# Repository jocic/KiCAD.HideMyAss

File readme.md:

# HideMyAss

**Song of the project:** [Judas Priest - Breaking The Law](https://www.youtube.com/watch?v=L397TWLwrUU)

*  LoJack (173 MHz)
*  SM (925 – 960 MHz)
*  DCS (1805 – 1880 MHz)
*  3G (2100 – 2170 MHz )
*  4G Low (790 – 870 MHz)
*  4G High (2600 – 2690 MHz)
*  5G F1 (450 MHz to 6 GHz)
*  5G F2 (24.25 GHz to 52.6 GHz)
*  WiFi (2400 – 2500 MHz)
*  GPS L1 (1570 – 1580 MHz)
*  GPS L2 (1220 – 1230 MHz)
*  Bluetooth (2.402 GHz - 2.480 GHz)

When finished, device can be ordered directly from my website.

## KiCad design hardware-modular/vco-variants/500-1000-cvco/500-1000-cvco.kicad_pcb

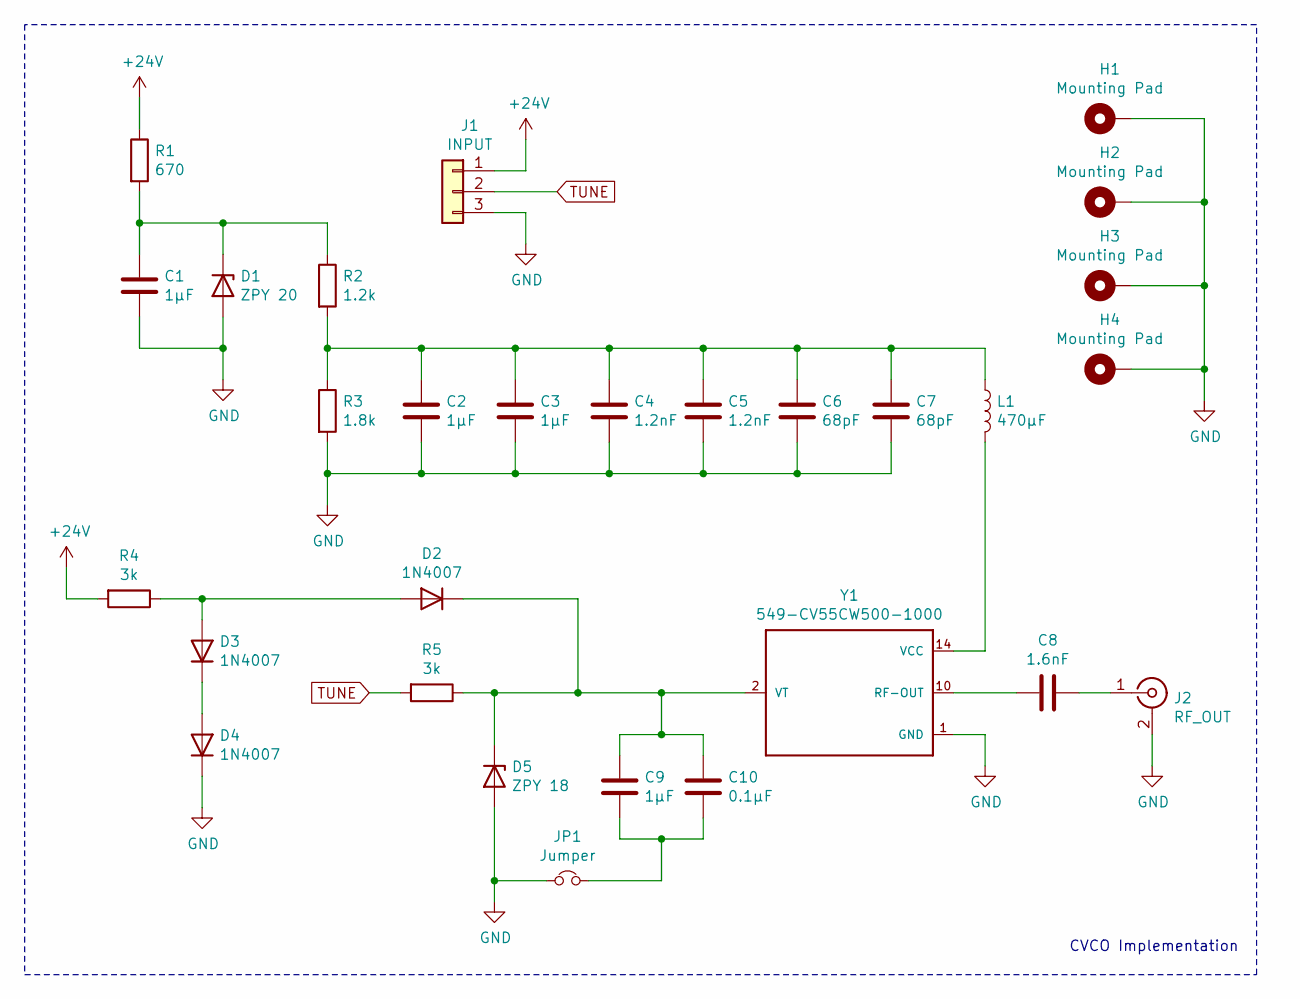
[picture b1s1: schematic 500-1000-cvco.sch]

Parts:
C1: 1μF; C_Disc_D3.0mm_W1.6mm_P2.50mm
C2, C3, C9: 1μF; C_0805_2012Metric
C4, C5: 1.2nF; C_0805_2012Metric
C6, C7: 68pF; C_0805_2012Metric
C8: 1.6nF; C_0805_2012Metric
C10: 0.1μF; C_0805_2012Metric
D1: ZPY 20; D_DO-41_SOD81_P2.54mm_Vertical_AnodeUp
D2, D3, D4: 1N4007; D_DO-41_SOD81_P2.54mm_Vertical_AnodeUp
D5: ZPY 18; D_DO-41_SOD81_P2.54mm_Vertical_AnodeUp
H1, H2, H3, H4: Mounting Pad; MountingHole_3.2mm_M3_Pad_Via
J1: INPUT; TerminalBlock_4Ucon_1x03_P3.50mm_Vertical
J2: RF_OUT; SMA_Amphenol_132289_EdgeMount
JP1: Jumper; PinHeader_1x02_P2.54mm_Vertical
L1: 470μF; L_0805_2012Metric
R1: 670; R_Axial_DIN0309_L9.0mm_D3.2mm_P15.24mm_Horizontal
R2: 1.2k; R_Axial_DIN0207_L6.3mm_D2.5mm_P10.16mm_Horizontal
R3: 1.8k; R_Axial_DIN0207_L6.3mm_D2.5mm_P10.16mm_Horizontal
R4, R5: 3k; R_Axial_DIN0207_L6.3mm_D2.5mm_P10.16mm_Horizontal
Y1: 549-CV55CW500-1000; CVCO55

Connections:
+24V: J1.1, R1.1, R4.2
GND: C1.2, C2.2, C3.2, C4.2, C5.2, C6.2, C7.2, D1.2 (A), D4.1 (K), D5.2 (A), H1.1, H2.1, H3.1, H4.1, J1.3, J2.2 (Ext), JP1.1, R3.2, Y1.1 (GND), Y1.3 (GND), Y1.4 (GND), Y1.5 (GND), Y1.6 (GND), Y1.7 (GND), Y1.8 (GND), Y1.9 (GND), Y1.11 (GND), Y1.12 (GND), Y1.13 (GND), Y1.15 (GND), Y1.16 (GND)
unnamed: C1.1, D1.1 (K), R1.2, R2.1
unnamed: C2.1, C3.1, C4.1, C5.1, C6.1, C7.1, L1.1, R2.2, R3.1
unnamed: C8.1, J2.1 (In)
unnamed: C8.2, Y1.10 (RF-OUT)
unnamed: C9.1, C10.1, D2.1 (K), D5.1 (K), R5.1, Y1.2 (VT)
unnamed: C9.2, C10.2, JP1.2
unnamed: D2.2 (A), D3.2 (A), R4.1
unnamed: D3.1 (K), D4.2 (A)
unnamed: L1.2, Y1.14 (VCC)
TUNE: J1.2, R5.2

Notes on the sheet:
CVCO Implementation

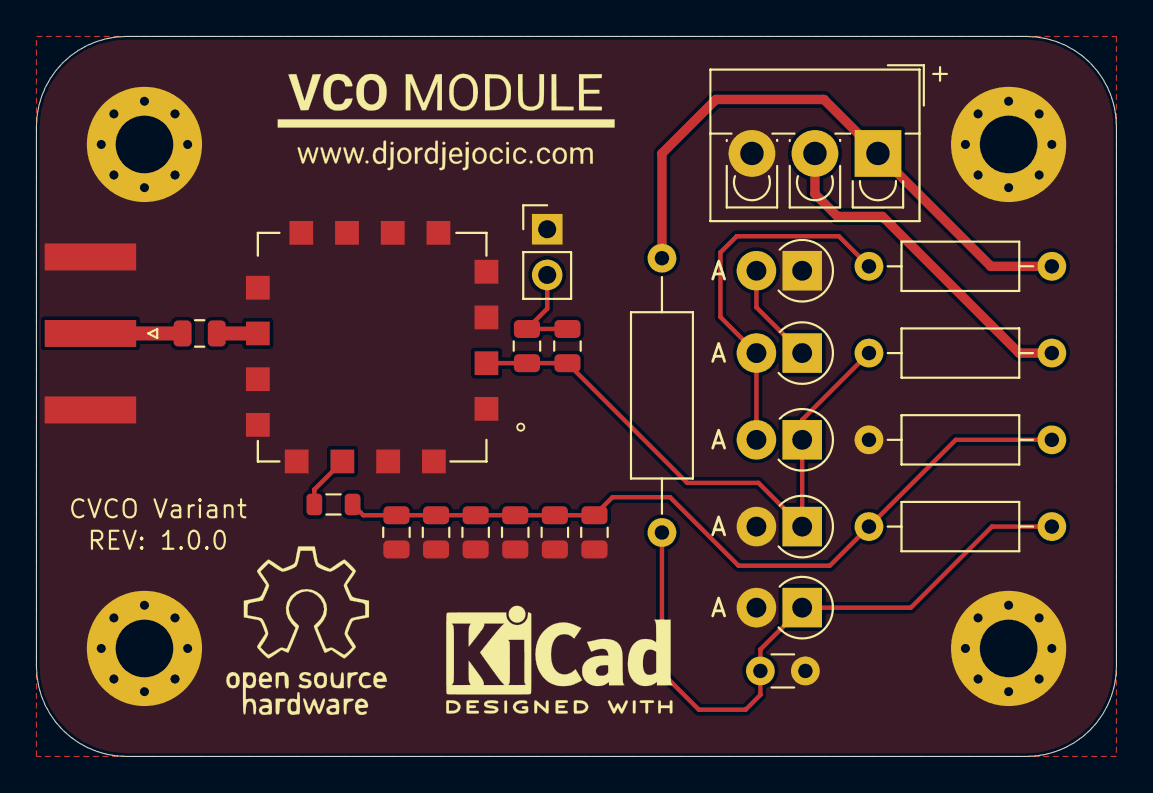
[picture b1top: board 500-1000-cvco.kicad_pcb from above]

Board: 2 copper layers, 60.0 x 40.0 mm, 29 parts (0 on the bottom side), 12 nets.

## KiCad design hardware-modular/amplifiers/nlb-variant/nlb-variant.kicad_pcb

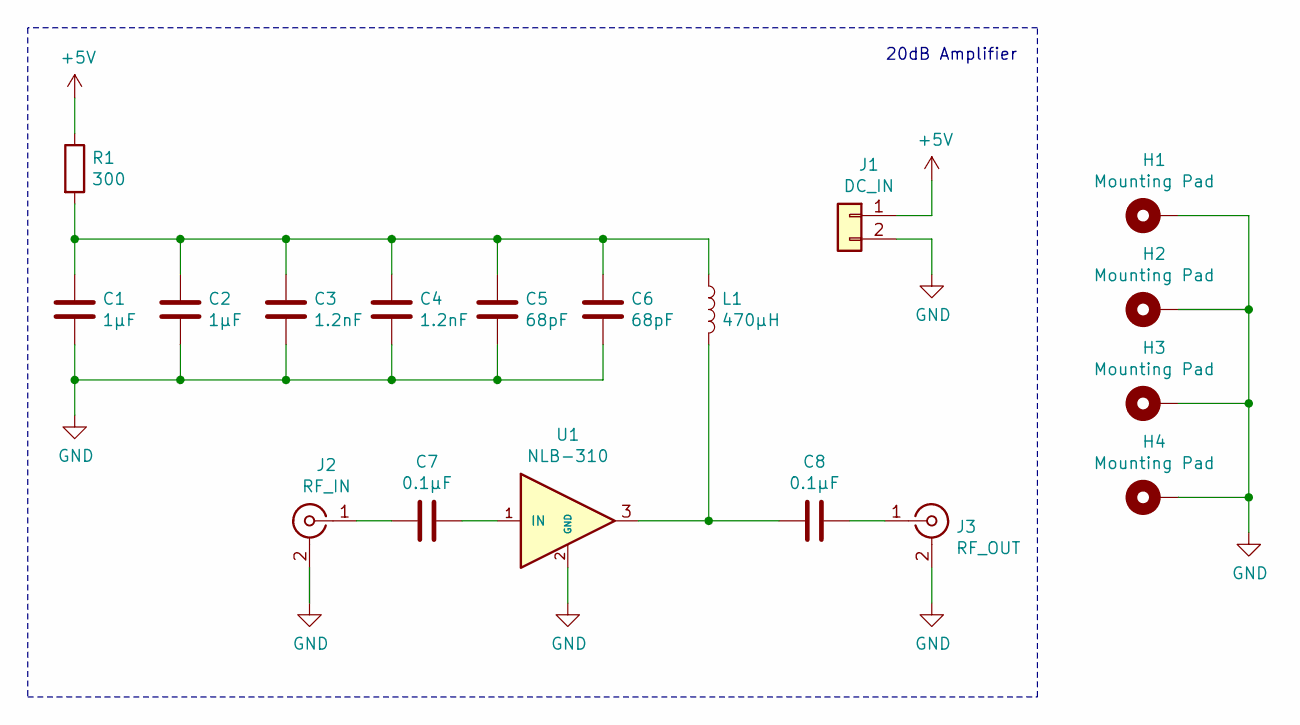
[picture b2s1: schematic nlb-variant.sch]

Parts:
C1, C2: 1μF; C_0805_2012Metric
C3, C4: 1.2nF; C_0805_2012Metric
C5, C6: 68pF; C_0805_2012Metric
C7, C8: 0.1μF; C_0805_2012Metric
H1, H2, H3, H4: Mounting Pad; MountingHole_3.2mm_M3_Pad_Via
J1: DC_IN; TerminalBlock_4Ucon_1x02_P3.50mm_Horizontal
J2: RF_IN; SMA_Amphenol_132289_EdgeMount
J3: RF_OUT; SMA_Amphenol_132289_EdgeMount
L1: 470μH; L_0805_2012Metric
R1: 300; R_0805_2012Metric
U1: NLB-310; Micro-X-4

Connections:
+5V: J1.1, R1.1
GND: C1.2, C2.2, C3.2, C4.2, C5.2, C6.2, H1.1, H2.1, H3.1, H4.1, J1.2, J2.2 (Ext), J3.2 (Ext), U1.2 (GND), U1.4 (GND)
unnamed: C1.1, C2.1, C3.1, C4.1, C5.1, C6.1, L1.1, R1.2
unnamed: C7.1, J2.1 (In)
unnamed: C7.2, U1.1 (IN)
unnamed: C8.1, L1.2, U1.3
unnamed: C8.2, J3.1 (In)

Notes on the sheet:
20dB Amplifier

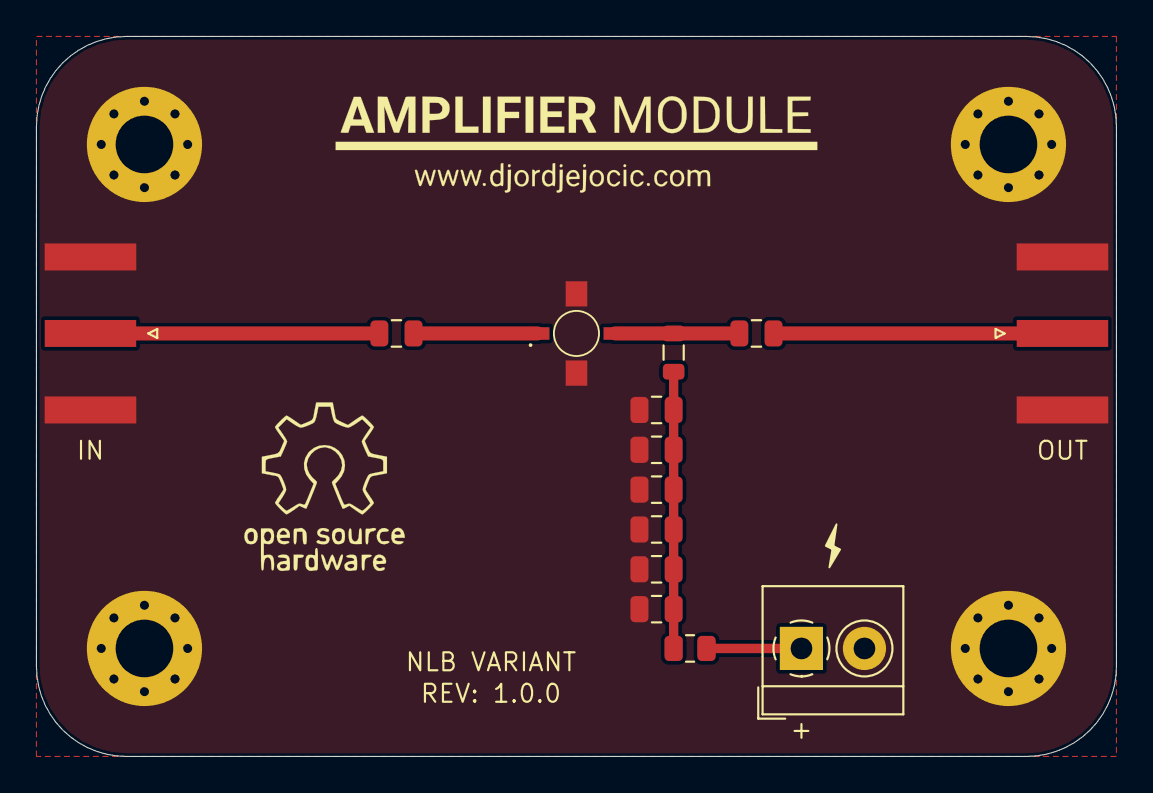
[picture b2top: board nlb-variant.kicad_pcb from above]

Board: 2 copper layers, 60.0 x 40.0 mm, 18 parts (0 on the bottom side), 7 nets.

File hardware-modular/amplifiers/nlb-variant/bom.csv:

Reference, Quantity, Value, Footprint, Datasheet
C1 C2 ,2,"1μF","Capacitor_SMD:C_0805_2012Metric","~"
C3 C4 ,2,"1.2nF","Capacitor_SMD:C_0805_2012Metric","~"
C5 C6 ,2,"68pF","Capacitor_SMD:C_0805_2012Metric","~"
C7 C8 ,2,"0.1μF","Capacitor_SMD:C_0805_2012Metric","~"
H1 H2 H3 H4 ,4,"Mounting Pad","MountingHole:MountingHole_3.2mm_M3_Pad_Via","~"
J1 ,1,"DC_IN","TerminalBlock_4Ucon:TerminalBlock_4Ucon_1x02_P3.50mm_Horizontal","~"
J2 ,1,"RF_IN","Connector_Coaxial:SMA_Amphenol_132289_EdgeMount"," ~"
J3 ,1,"RF_OUT","Connector_Coaxial:SMA_Amphenol_132289_EdgeMount"," ~"
L1 ,1,"470μH","Inductor_SMD:L_0805_2012Metric","~"
R1 ,1,"300","Resistor_SMD:R_0805_2012Metric","~"
U1 ,1,"NLB-310","CVCO:Micro-X-4",""

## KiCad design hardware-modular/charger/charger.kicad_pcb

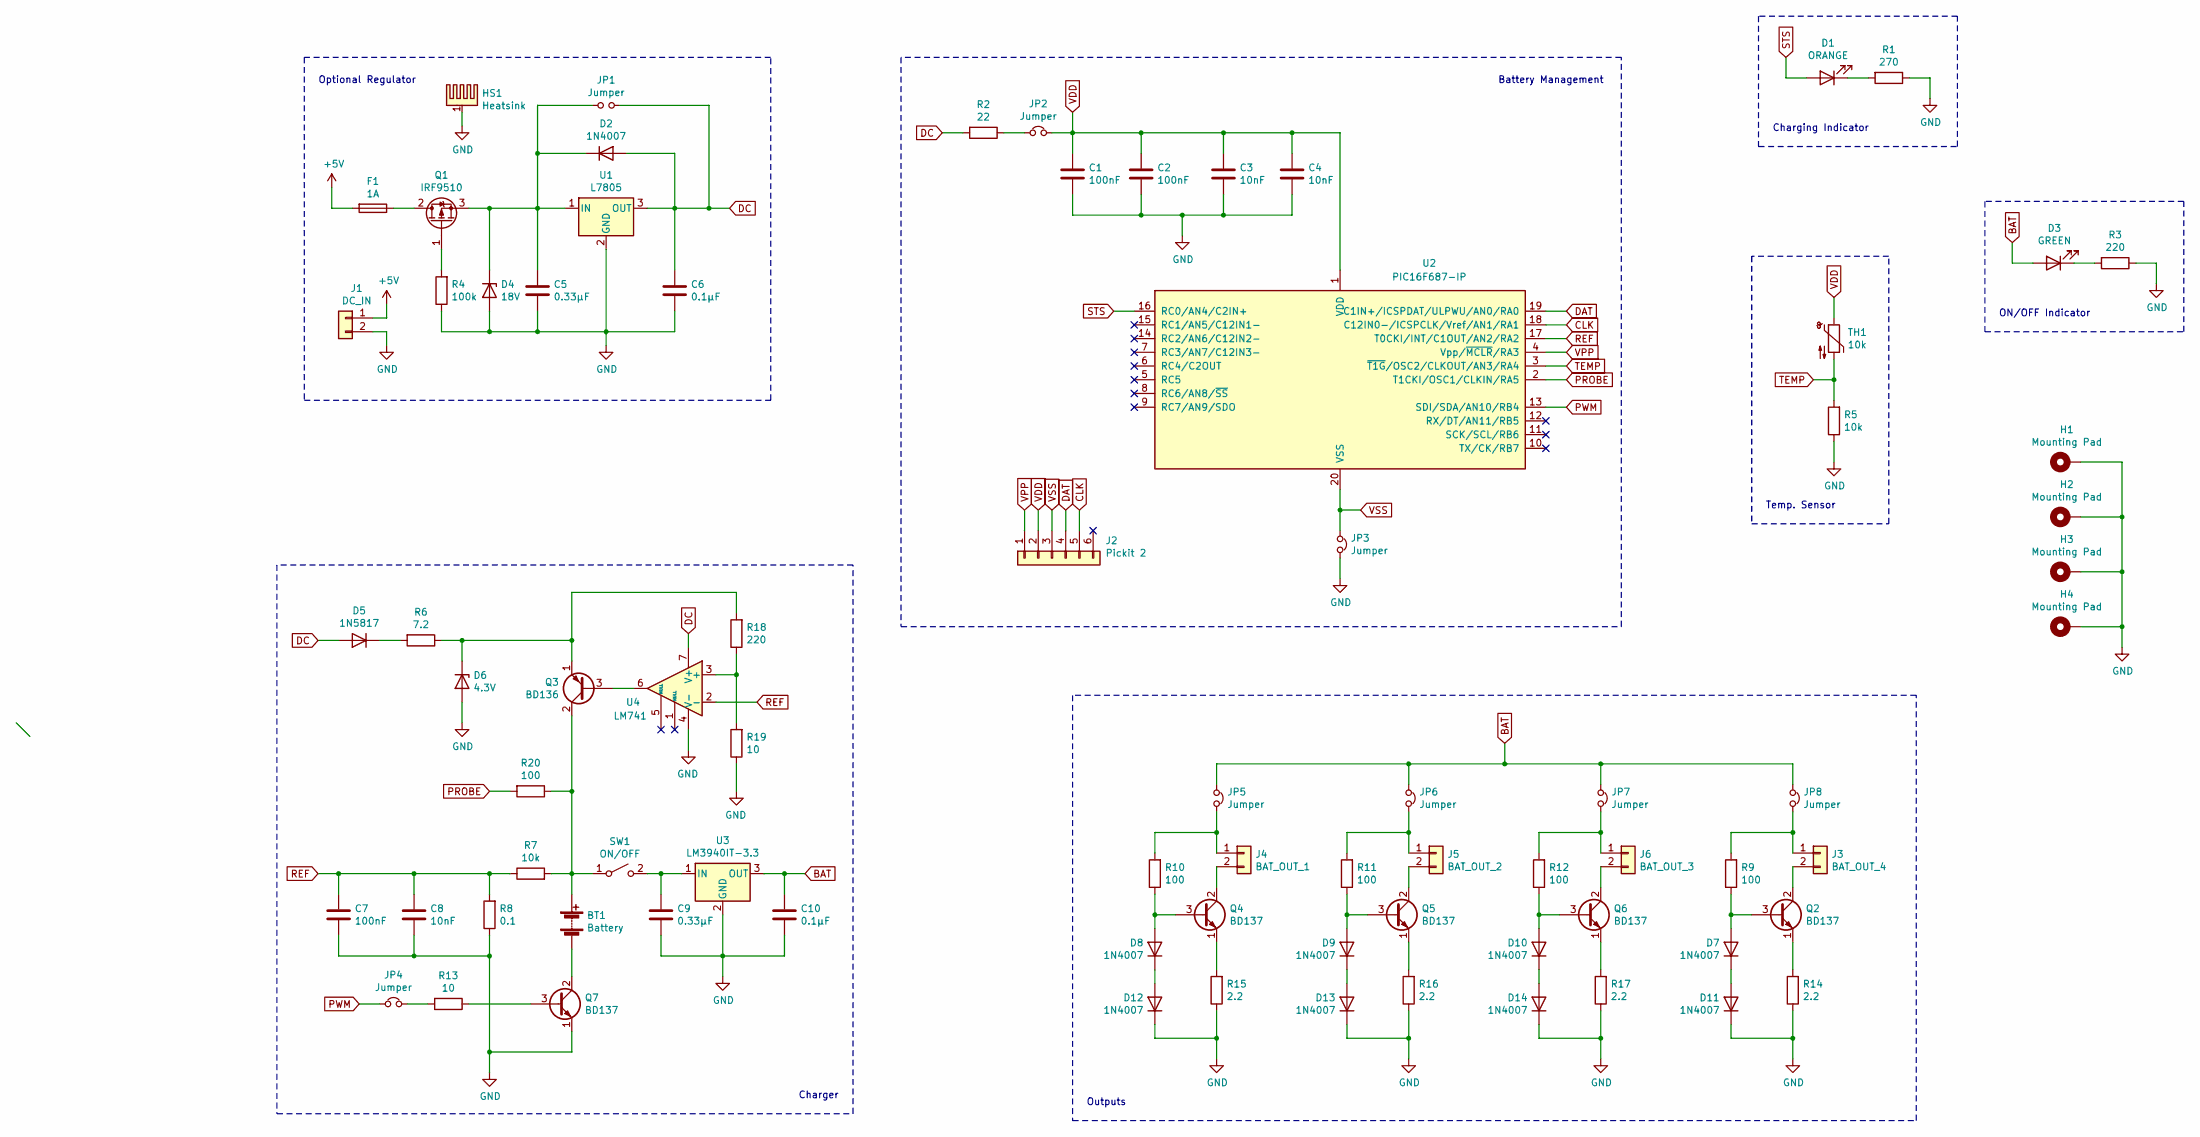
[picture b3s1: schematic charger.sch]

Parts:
BT1: Battery; TerminalBlock_4Ucon_1x02_P3.50mm_Horizontal
C1, C2, C7: 100nF; C_Disc_D3.0mm_W1.6mm_P2.50mm
C3, C4, C8: 10nF; C_Disc_D3.0mm_W1.6mm_P2.50mm
C5, C9: 0.33μF; C_Disc_D3.0mm_W1.6mm_P2.50mm
C6, C10: 0.1μF; C_Disc_D3.0mm_W1.6mm_P2.50mm
D1: ORANGE; Molex_KK-254_AE-6410-02A_1x02_P2.54mm_Vertical
D2, D7, D8, D9, D10, D11, D12, D13, D14: 1N4007; D_DO-41_SOD81_P10.16mm_Horizontal
D3: GREEN; Molex_KK-254_AE-6410-02A_1x02_P2.54mm_Vertical
D4: 18V; D_DO-41_SOD81_P10.16mm_Horizontal
D5: 1N5817; D_DO-41_SOD81_P10.16mm_Horizontal
D6: 4.3V; D_DO-41_SOD81_P10.16mm_Horizontal
F1: 1A; Fuseholder_Cylinder-5x20mm_Stelvio-Kontek_PTF78_Horizontal_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
H1, H2, H3, H4: Mounting Pad; MountingHole_3.2mm_M3_Pad_Via
HS1: Heatsink; Heatsink_Fischer_SK104-STCB_35x13mm__2xDrill3.5mm_ScrewM3
J1: DC_IN; TerminalBlock_4Ucon_1x02_P3.50mm_Horizontal
J2: Pickit 2; PinSocket_1x06_P2.54mm_Vertical
J3: BAT_OUT_4; TerminalBlock_4Ucon_1x02_P3.50mm_Horizontal
J4: BAT_OUT_1; TerminalBlock_4Ucon_1x02_P3.50mm_Horizontal
J5: BAT_OUT_2; TerminalBlock_4Ucon_1x02_P3.50mm_Horizontal
J6: BAT_OUT_3; TerminalBlock_4Ucon_1x02_P3.50mm_Horizontal
JP1, JP2, JP3, JP4, JP5, JP6, JP7, JP8: Jumper; PinHeader_1x02_P2.54mm_Vertical
Q1: IRF9510; TO-220-3_Vertical
Q2, Q4, Q5, Q6, Q7: BD137; TO-126-3_Vertical
Q3: BD136; TO-126-3_Vertical
R1: 270; R_Axial_DIN0207_L6.3mm_D2.5mm_P10.16mm_Horizontal
R2: 22; R_Axial_DIN0414_L11.9mm_D4.5mm_P5.08mm_Vertical
R3, R18: 220; R_Axial_DIN0207_L6.3mm_D2.5mm_P10.16mm_Horizontal
R4: 100k; R_Axial_DIN0207_L6.3mm_D2.5mm_P10.16mm_Horizontal
R5, R7: 10k; R_Axial_DIN0207_L6.3mm_D2.5mm_P10.16mm_Horizontal
R6: 7.2; R_Axial_DIN0516_L15.5mm_D5.0mm_P5.08mm_Vertical
R8: 0.1; R_Axial_DIN0207_L6.3mm_D2.5mm_P10.16mm_Horizontal
R9, R10, R11, R12, R20: 100; R_Axial_DIN0207_L6.3mm_D2.5mm_P10.16mm_Horizontal
R13, R19: 10; R_Axial_DIN0207_L6.3mm_D2.5mm_P10.16mm_Horizontal
R14, R15, R16, R17: 2.2; R_Axial_DIN0207_L6.3mm_D2.5mm_P10.16mm_Horizontal
SW1: ON/OFF; Molex_KK-254_AE-6410-02A_1x02_P2.54mm_Vertical
TH1: 10k; Molex_KK-254_AE-6410-02A_1x02_P2.54mm_Vertical
U1: L7805; TO-220-3_Vertical
U2: PIC16F687-IP; DIP-20_W7.62mm_Socket
U3: LM3940IT-3.3; TO-220-3_Vertical
U4: LM741; DIP-8_W7.62mm_Socket

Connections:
+5V: F1.2, J1.1
BAT: C10.1, D3.2 (A), JP5.1, JP6.1, JP7.1, JP8.1, U3.3 (OUT)
CLK: J2.5, U2.18 (C12IN0-/ICSPCLK/Vref/AN1/RA1)
DAT: J2.4, U2.19 (C1IN+/ICSPDAT/ULPWU/AN0/RA0)
DC: C6.1, D2.2 (A), D5.2 (A), JP1.2, R2.2, U1.3 (OUT), U4.7 (V+)
GND: C1.2, C2.2, C3.2, C4.2, C5.2, C6.2, C7.2, C8.2, C9.2, C10.2, D4.2 (A), D6.2 (A), D11.1 (K), D12.1 (K), D13.1 (K), D14.1 (K), H1.1, H2.1, H3.1, H4.1, HS1.1, J1.2, JP3.2, Q7.1 (E), R1.1, R3.1, R4.1, R5.1, R8.1, R14.1, R15.1, R16.1, R17.1, R19.1, U1.2 (GND), U3.2 (GND), U4.4 (V-)
unnamed: BT1.1 (+), Q3.2 (C), R7.2, R20.1, SW1.1 (A)
unnamed: BT1.2 (-), Q7.2 (C)
unnamed: C5.1, D2.1 (K), D4.1 (K), JP1.1, Q1.3 (S), U1.1 (IN)
unnamed: C9.1, SW1.2 (B), U3.1 (IN)
unnamed: D1.1 (K), R1.2
unnamed: D3.1 (K), R3.2
unnamed: D5.1 (K), R6.2
unnamed: D6.1 (K), Q3.1 (E), R6.1, R18.2
unnamed: D7.2 (A), Q2.3 (B), R9.1
unnamed: D8.2 (A), Q4.3 (B), R10.1
unnamed: D9.2 (A), Q5.3 (B), R11.1
unnamed: D10.1 (K), D14.2 (A)
unnamed: D10.2 (A), Q6.3 (B), R12.1
unnamed: D7.1 (K), D11.2 (A)
unnamed: D8.1 (K), D12.2 (A)
unnamed: D9.1 (K), D13.2 (A)
unnamed: F1.1, Q1.2 (D)
unnamed: J3.1, JP8.2, R9.2
unnamed: J3.2, Q2.2 (C)
unnamed: J4.1, JP5.2, R10.2
unnamed: J4.2, Q4.2 (C)
unnamed: J5.1, JP6.2, R11.2
unnamed: J5.2, Q5.2 (C)
unnamed: J6.1, JP7.2, R12.2
unnamed: J6.2, Q6.2 (C)
unnamed: JP2.1, R2.1
unnamed: JP4.2, R13.2
unnamed: Q1.1 (G), R4.2
unnamed: Q2.1 (E), R14.2
unnamed: Q3.3 (B), U4.6
unnamed: Q4.1 (E), R15.2
unnamed: Q5.1 (E), R16.2
unnamed: Q6.1 (E), R17.2
unnamed: Q7.3 (B), R13.1
unnamed: R18.1, R19.2, U4.3 (+)
PROBE: R20.2, U2.2 (T1CKI/OSC1/CLKIN/RA5)
PWM: JP4.1, U2.13 (SDI/SDA/AN10/RB4)
REF: C7.1, C8.1, R7.1, R8.2, U2.17 (T0CKI/INT/C1OUT/AN2/RA2), U4.2 (-)
STS: D1.2 (A), U2.16 (RC0/AN4/C2IN+)
TEMP: R5.2, TH1.2, U2.3 (~T1G~/OSC2/CLKOUT/AN3/RA4)
VDD: C1.1, C2.1, C3.1, C4.1, J2.2, JP2.2, TH1.1, U2.1 (VDD)
VPP: J2.1, U2.4 (Vpp/~MCLR~/RA3)
VSS: J2.3, JP3.1, U2.20 (VSS)

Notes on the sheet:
Charging Indicator
Temp. Sensor
Optional Regulator
Battery Management
ON/OFF Indicator
Outputs
Charger

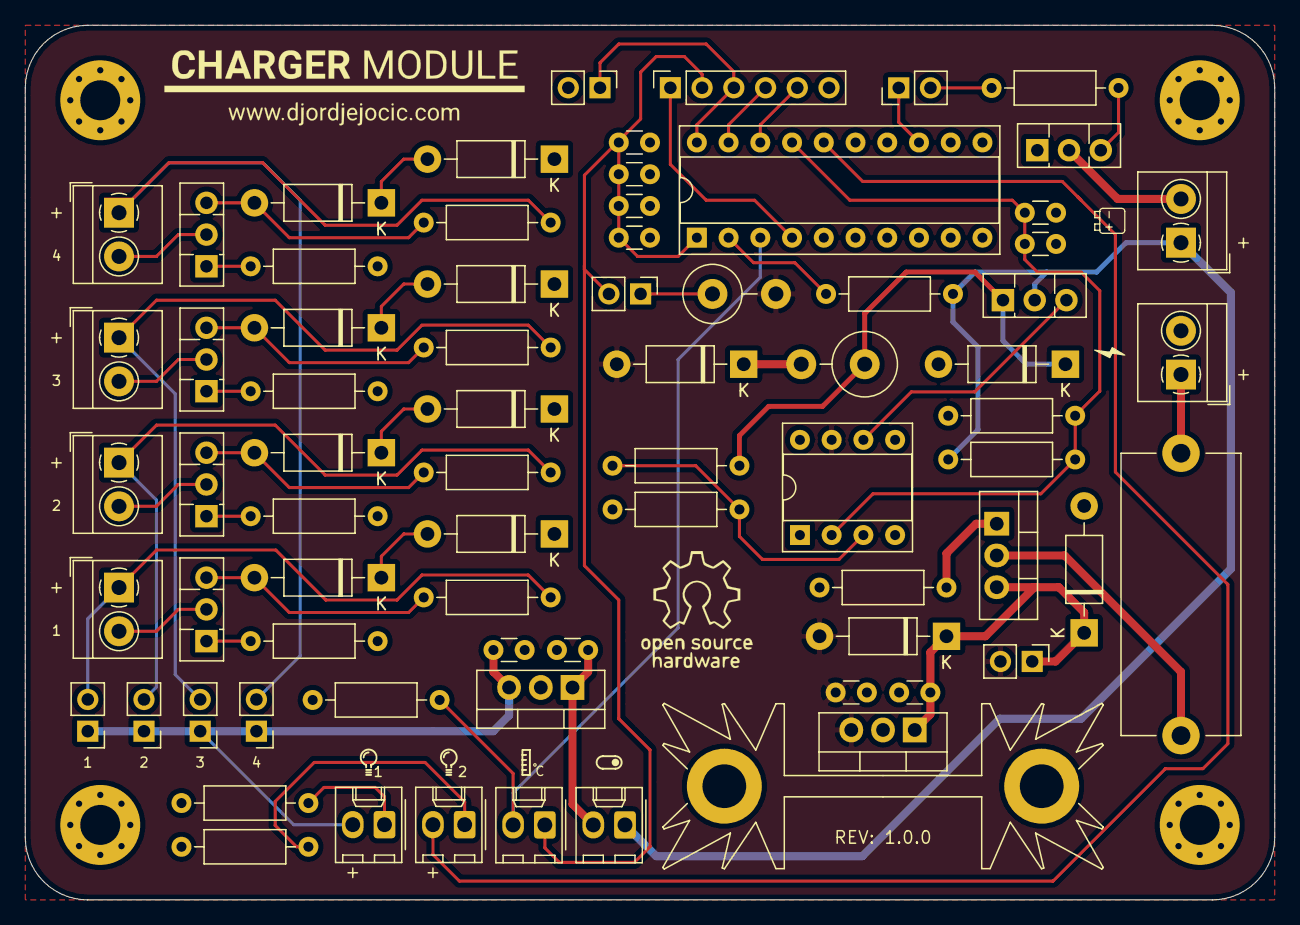
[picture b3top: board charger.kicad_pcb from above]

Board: 2 copper layers, 100.0 x 70.0 mm, 78 parts (0 on the bottom side), 49 nets.

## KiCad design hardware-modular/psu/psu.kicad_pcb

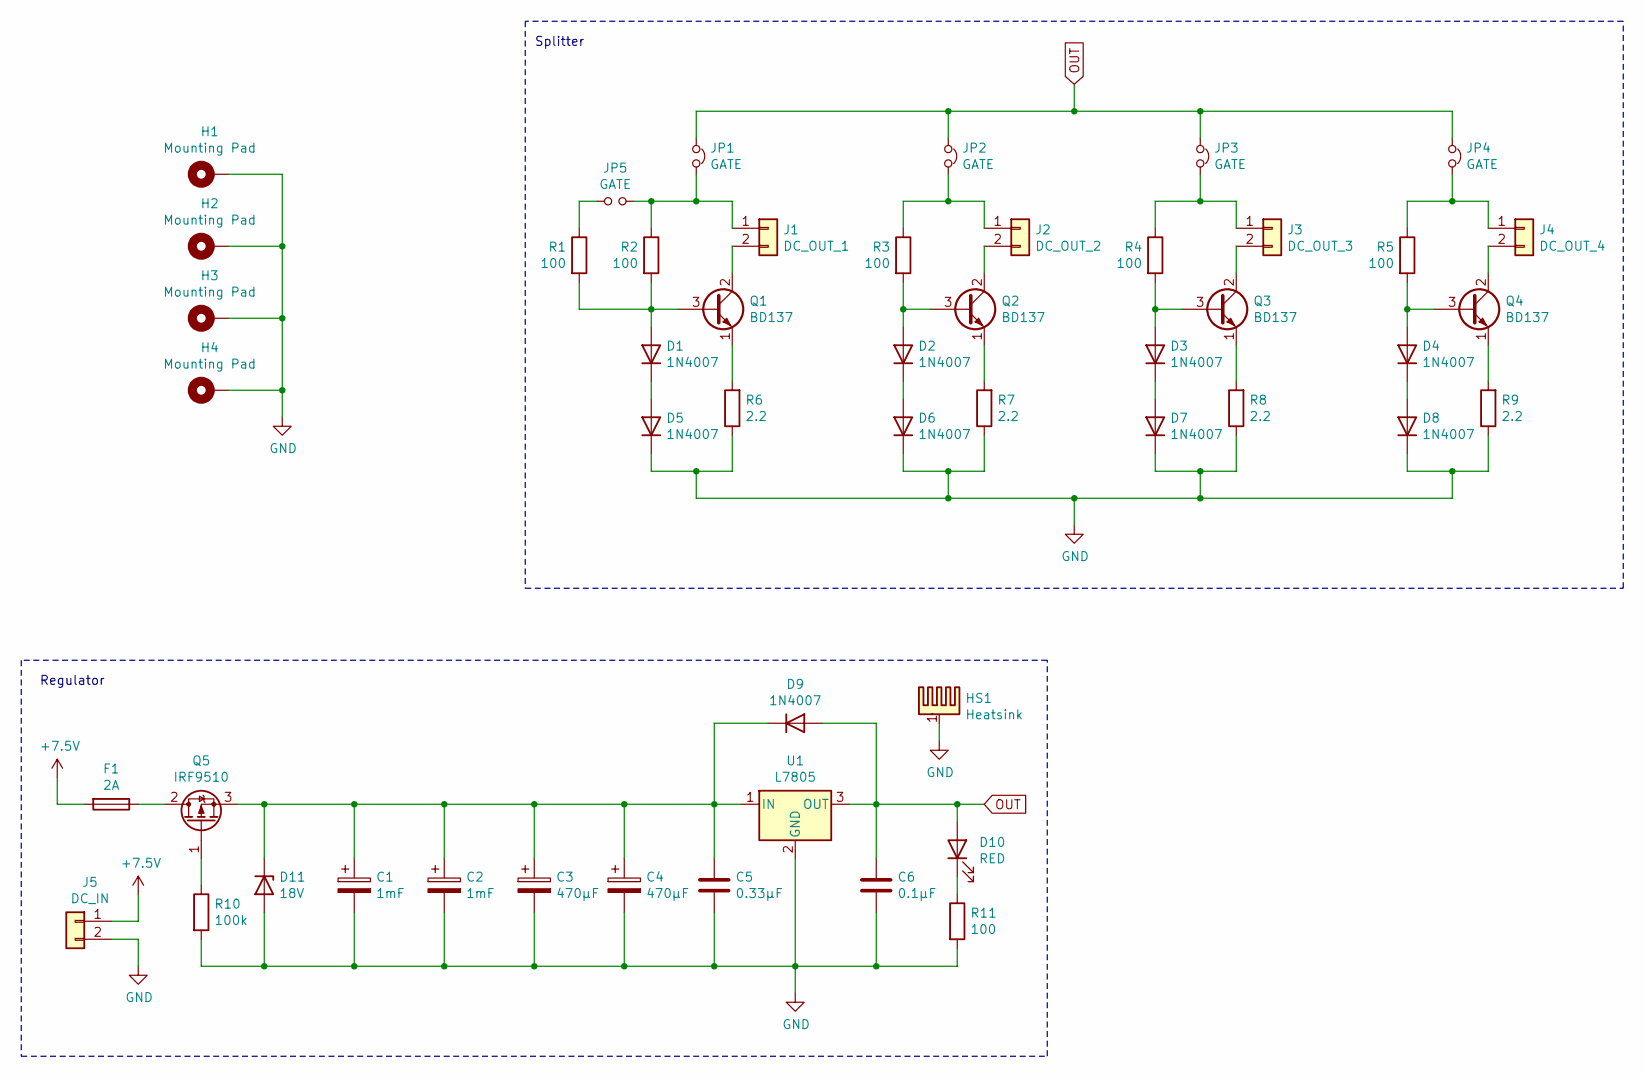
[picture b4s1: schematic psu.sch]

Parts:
C1, C2: 1mF; CP_Radial_D10.0mm_P5.00mm
C3, C4: 470µF; CP_Radial_D10.0mm_P5.00mm
C5: 0.33µF; C_Disc_D3.0mm_W1.6mm_P2.50mm
C6: 0.1µF; C_Disc_D3.0mm_W1.6mm_P2.50mm
D1, D2, D3, D4, D5, D6, D7, D8, D9: 1N4007; D_DO-41_SOD81_P10.16mm_Horizontal
D10: RED; Molex_KK-254_AE-6410-02A_1x02_P2.54mm_Vertical
D11: 18V; D_DO-41_SOD81_P10.16mm_Horizontal
F1: 2A; Fuseholder_Cylinder-5x20mm_Stelvio-Kontek_PTF78_Horizontal_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
H1, H2, H3, H4: Mounting Pad; MountingHole_3.2mm_M3_Pad_Via
HS1: Heatsink; Heatsink_Fischer_SK104-STCB_35x13mm__2xDrill3.5mm_ScrewM3
J1: DC_OUT_1; TerminalBlock_4Ucon_1x02_P3.50mm_Horizontal
J2: DC_OUT_2; TerminalBlock_4Ucon_1x02_P3.50mm_Horizontal
J3: DC_OUT_3; TerminalBlock_4Ucon_1x02_P3.50mm_Horizontal
J4: DC_OUT_4; TerminalBlock_4Ucon_1x02_P3.50mm_Horizontal
J5: DC_IN; TerminalBlock_4Ucon_1x02_P3.50mm_Horizontal
JP1, JP2, JP3, JP4, JP5: GATE; PinHeader_1x02_P2.54mm_Vertical
Q1, Q2, Q3, Q4: BD137; TO-126-3_Vertical
Q5: IRF9510; TO-220-3_Vertical
R1, R2, R3, R4, R5, R11: 100; R_Axial_DIN0207_L6.3mm_D2.5mm_P10.16mm_Horizontal
R6, R7, R8, R9: 2.2; R_Axial_DIN0207_L6.3mm_D2.5mm_P10.16mm_Horizontal
R10: 100k; R_Axial_DIN0207_L6.3mm_D2.5mm_P10.16mm_Horizontal
U1: L7805; TO-220-3_Vertical

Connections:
+7.5V: F1.2, J5.1
GND: C1.2, C2.2, C3.2, C4.2, C5.2, C6.2, D5.1 (K), D6.1 (K), D7.1 (K), D8.1 (K), D11.2 (A), H1.1, H2.1, H3.1, H4.1, HS1.1, J5.2, R6.1, R7.1, R8.1, R9.1, R10.2, R11.2, U1.2 (GND)
unnamed: C1.1, C2.1, C3.1, C4.1, C5.1, D9.1 (K), D11.1 (K), Q5.3 (S), U1.1 (IN)
unnamed: D1.1 (K), D5.2 (A)
unnamed: D1.2 (A), Q1.3 (B), R1.2, R2.2
unnamed: D2.1 (K), D6.2 (A)
unnamed: D2.2 (A), Q2.3 (B), R3.2
unnamed: D3.1 (K), D7.2 (A)
unnamed: D3.2 (A), Q3.3 (B), R4.2
unnamed: D4.1 (K), D8.2 (A)
unnamed: D4.2 (A), Q4.3 (B), R5.2
unnamed: D10.1 (K), R11.1
unnamed: F1.1, Q5.2 (D)
unnamed: J1.1, JP1.2, JP5.2, R2.1
unnamed: J1.2, Q1.2 (C)
unnamed: J2.1, JP2.2, R3.1
unnamed: J2.2, Q2.2 (C)
unnamed: J3.1, JP3.2, R4.1
unnamed: J3.2, Q3.2 (C)
unnamed: J4.1, JP4.2, R5.1
unnamed: J4.2, Q4.2 (C)
unnamed: JP5.1, R1.1
unnamed: Q1.1 (E), R6.2
unnamed: Q2.1 (E), R7.2
unnamed: Q3.1 (E), R8.2
unnamed: Q4.1 (E), R9.2
unnamed: Q5.1 (G), R10.1
OUT: C6.1, D9.2 (A), D10.2 (A), JP1.1, JP2.1, JP3.1, JP4.1, U1.3 (OUT)

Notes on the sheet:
Regulator
Splitter

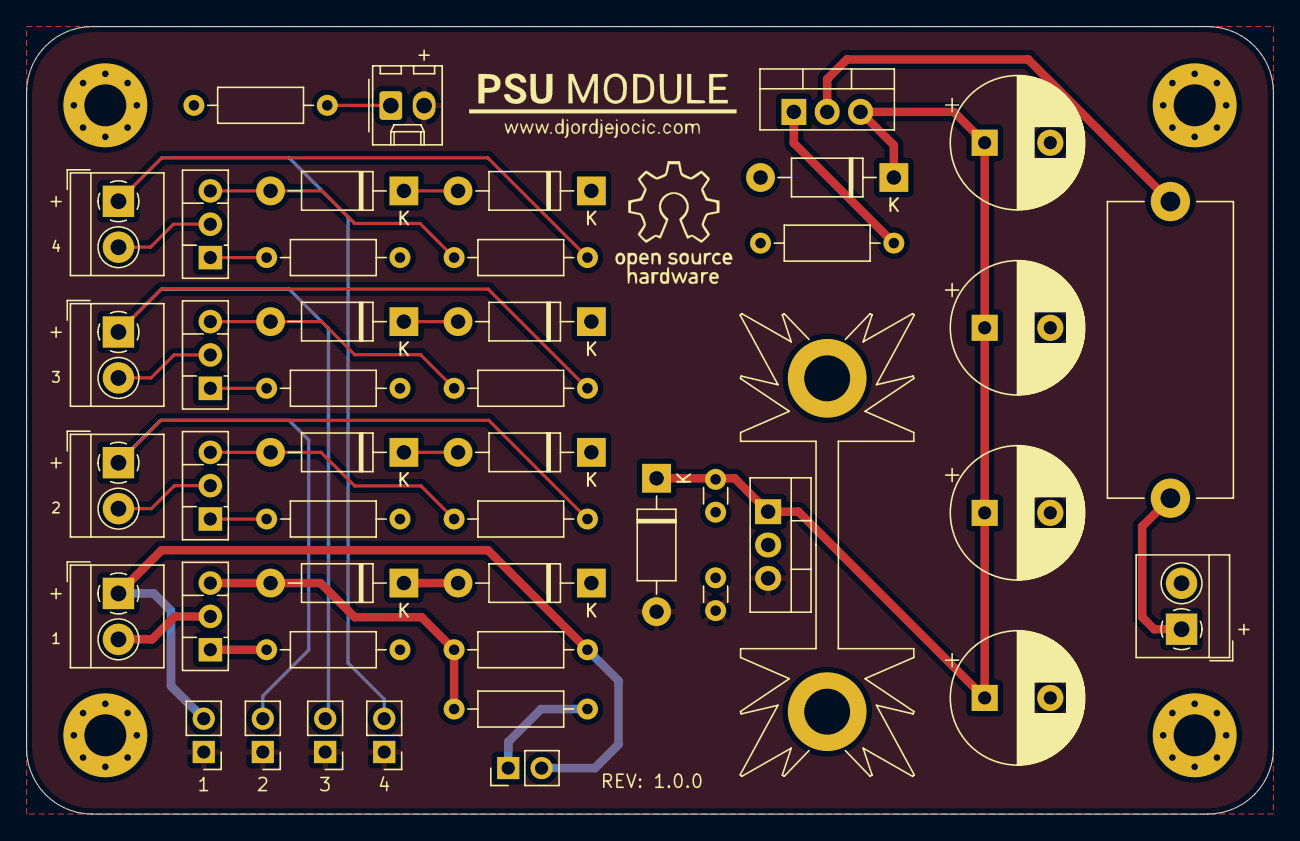
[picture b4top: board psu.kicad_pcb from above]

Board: 2 copper layers, 95.0 x 60.0 mm, 50 parts (0 on the bottom side), 28 nets.
